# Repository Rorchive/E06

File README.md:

<div align="center">
  
</div>

<h1 align="center">E06 Project - Analog Temperature Monitor</h1>

<p align="center">

</p>

<br>

## Overview

This project involves the development of an Analog Temperature Threshold Monitor tailored for the E06 (Analog Electronics 3) course at Inatel. The system senses temperature with an LM35 precision sensor (10 mV/°C). Its signal is conditioned by an LM324 operational amplifier in a non-inverting configuration with a gain of 10, which scales the output to 100 mV/°C. Two LM324 comparators with positive feedback (Schmitt trigger) classify the temperature into three bands: a green LED indicates T < 35 °C, a red LED indicates T > 58 °C, and both stay off in the normal range. Hysteresis of about 1 °C on each comparator eliminates output chattering caused by sensor noise near the thresholds. The green channel uses the inverting topology, and the red channel uses the non-inverting topology. Each threshold can be calibrated through Bourns 3362 trimpots, with series resistors that limit the adjustment range to ±10% for fine tuning. The hardware design runs on a symmetric ±15 V supply. It includes 1N4148 diodes that protect the LEDs against reverse voltage, an RC damper on the sensor output and local decoupling capacitors.

## Repository Organization

* `docs`: Project documentation.
* `hardware`: Native KiCad project and manufacturing files.
* `mechanics`: 3D models, technical drawings, and physical integration constraints.

## Releases

<table>
  <thead>
    <tr>
      <th>Render</th>
      <th>Hardware Revision</th>
      <th>Status</th>
      <th>Latest Release</th>
      <th>Date</th>
      <th>Datasheet</th>
      <th>BOM</th>
      <th>Manufacturing Info</th>
    </tr>
  </thead>
  <tbody>
    <tr>
      <td></td>
      <td>v1</td>
      <td>🚧 Development</td>
      <td><a href="#">-</a></td>
      <td>11-11-2026</td>
      <td><a href="#">-</a></td>
      <td><a href="#">-</a></td>
      <td><a href="#">-</a></td>
    </tr>
  </tbody>
</table>

## Fabrication

This board is intended to be fabricated using a chemical etching process. Both F.Cu and B.Cu layers are available in the [fabrication](hardware/fabrication/) folder.

## Contributing

We welcome contributions to this project! To ensure a smooth collaboration and maintain our engineering standards, please review our [Contribution Guidelines](CONTRIBUTING.md) before opening any issues, modifying the hardware design, or submitting pull requests.

## References

## License

The hardware designs and schematics are licensed under the permissive **[CERN-OHL-P-2.0](hardware/LICENSE)** open-hardware license. You are entirely free to use, modify, distribute, and commercialize the design without any copyleft obligations to share your derived works under the same terms.

---

<br/>

<div align="center">
  
</div>

<div align="center">
<sub>📜 This project is part of <strong><a href="https://github.com/Rorchive">Rorchive</a></strong>, my personal archive of activities and courses developed during my undergraduate studies at <strong>Inatel</strong>.</sub>

  <sub>Built with ❤️ by <a href="https://github.com/RodrigoCAndrade">Rodrigo Andrade</a></sub>
</div>

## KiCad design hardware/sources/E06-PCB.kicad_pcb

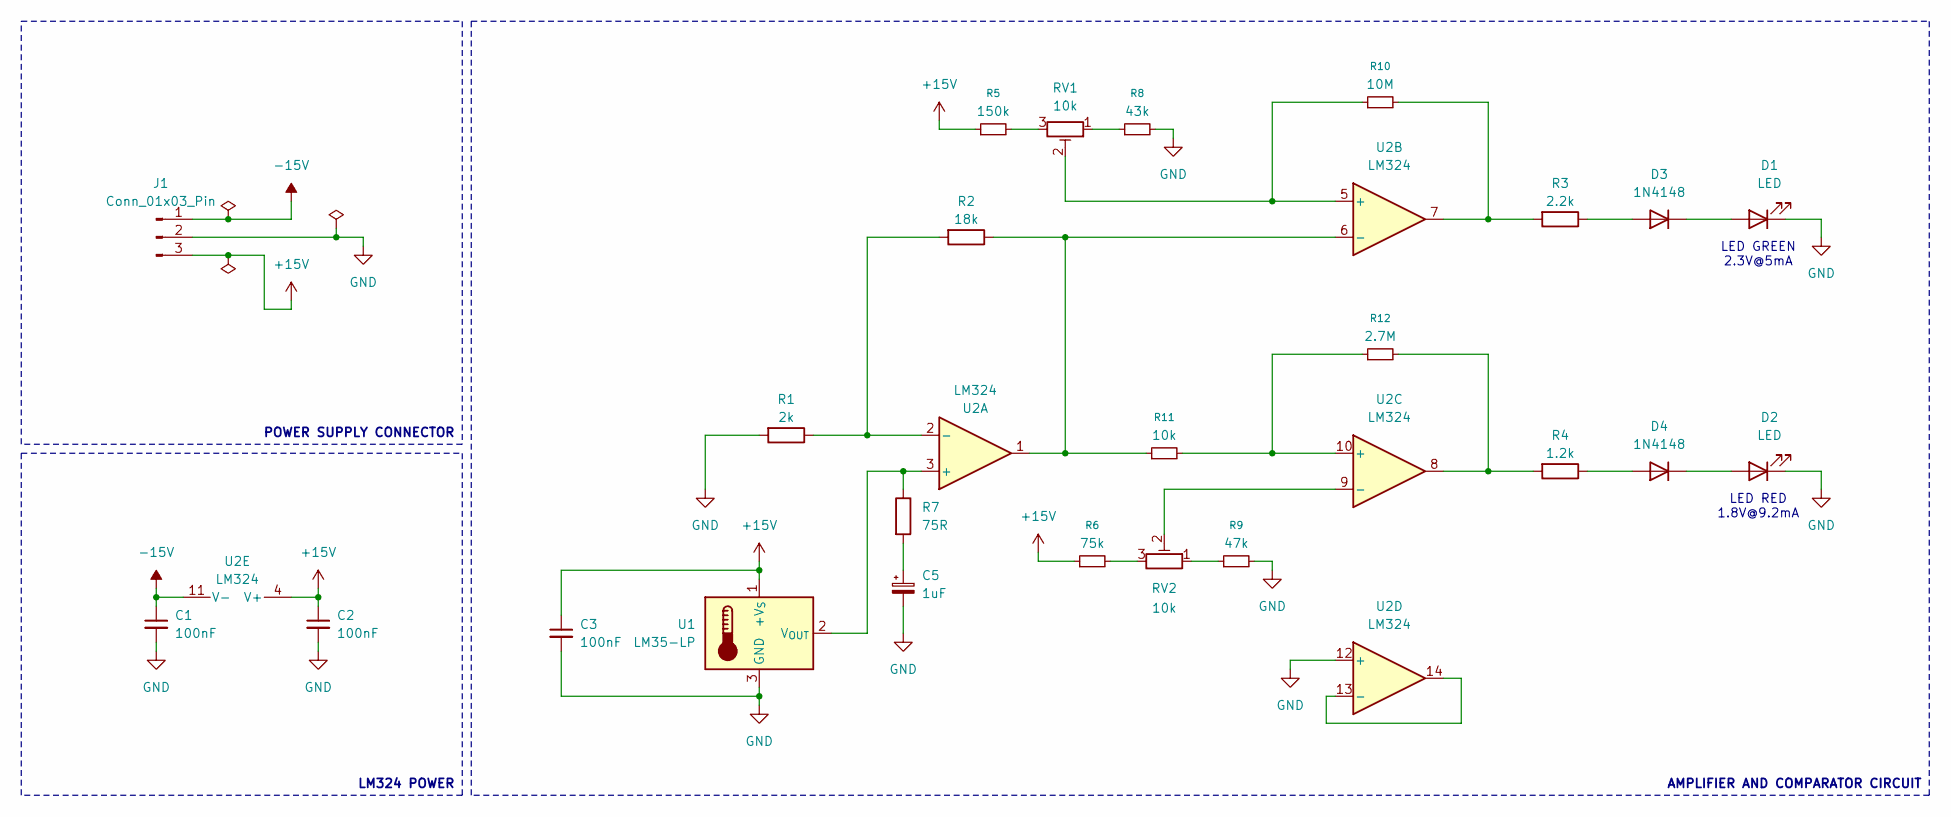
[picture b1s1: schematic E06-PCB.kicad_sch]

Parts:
C1, C2, C3: 100nF; C_Disc_D5.0mm_W2.5mm_P5.00mm
C5: 1uF; CP_Radial_D5.0mm_P2.00mm
D1, D2: LED; LED_D5.0mm
D3, D4: 1N4148; D_DO-35_SOD27_P7.62mm_Horizontal
J1: Conn_01x03_Pin; TerminalBlock_Phoenix_MKDS-1,5-3-5.08_1x03_P5.08mm_Horizont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
R1: 2k; R_Axial_DIN0207_L6.3mm_D2.5mm_P10.16mm_Horizontal
R2: 18k; R_Axial_DIN0207_L6.3mm_D2.5mm_P10.16mm_Horizontal
R3: 2.2k; R_Axial_DIN0207_L6.3mm_D2.5mm_P10.16mm_Horizontal
R4: 1.2k; R_Axial_DIN0207_L6.3mm_D2.5mm_P10.16mm_Horizontal
R5: 150k; R_Axial_DIN0207_L6.3mm_D2.5mm_P10.16mm_Horizontal
R6: 75k; R_Axial_DIN0207_L6.3mm_D2.5mm_P10.16mm_Horizontal
R7: 75R; R_Axial_DIN0207_L6.3mm_D2.5mm_P10.16mm_Horizontal
R8: 43k; R_Axial_DIN0207_L6.3mm_D2.5mm_P10.16mm_Horizontal
R9: 47k; R_Axial_DIN0207_L6.3mm_D2.5mm_P10.16mm_Horizontal
R10: 10M; R_Axial_DIN0207_L6.3mm_D2.5mm_P10.16mm_Horizontal
R11: 10k; R_Axial_DIN0207_L6.3mm_D2.5mm_P10.16mm_Horizontal
R12: 2.7M; R_Axial_DIN0207_L6.3mm_D2.5mm_P10.16mm_Horizontal
RV1, RV2: 10k; TRIM_3362P-1-103LF
U1: LM35-LP; TO-92_Wide
U2: LM324; SOIC-14_3.9x8.7mm_P1.27mm

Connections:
+15V: C2.1, C3.1, J1.3, R5.1, R6.1, U1.1 (+V_{S}), U2.4 (V+)
-15V: C1.1, J1.1, U2.11 (V-)
GND: C1.2, C2.2, C3.2, C5.2, D1.1 (K), D2.1 (K), J1.2, R1.2, R8.2, R9.2, U1.3 (GND), U2.12 (+)
unnamed: C5.1, R7.2
unnamed: D1.2 (A), D3.1 (K)
unnamed: D2.2 (A), D4.1 (K)
unnamed: D3.2 (A), R3.1
unnamed: D4.2 (A), R4.1
unnamed: R5.2, RV1.3
unnamed: R6.2, RV2.3
unnamed: R8.1, RV1.1
unnamed: R9.1, RV2.1
unnamed: R3.2, R10.2, U2.7
unnamed: R4.2, R12.2, U2.8
unnamed: R7.1, U1.2 (V_{OUT}), U2.3 (+)
unnamed: R1.1, R2.2, U2.2 (-)
unnamed: R10.1, RV1.2, U2.5 (+)
unnamed: R2.1, R11.1, U2.1, U2.6 (-)
unnamed: R11.2, R12.1, U2.10 (+)
unnamed: RV2.2, U2.9 (-)
unnamed: U2.13 (-), U2.14

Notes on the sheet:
LED RED 1.8V@9.2mA
LED GREEN 2.3V@5mA
AMPLIFIER AND COMPARATOR CIRCUIT
LM324 POWER
POWER SUPPLY CONNECTOR

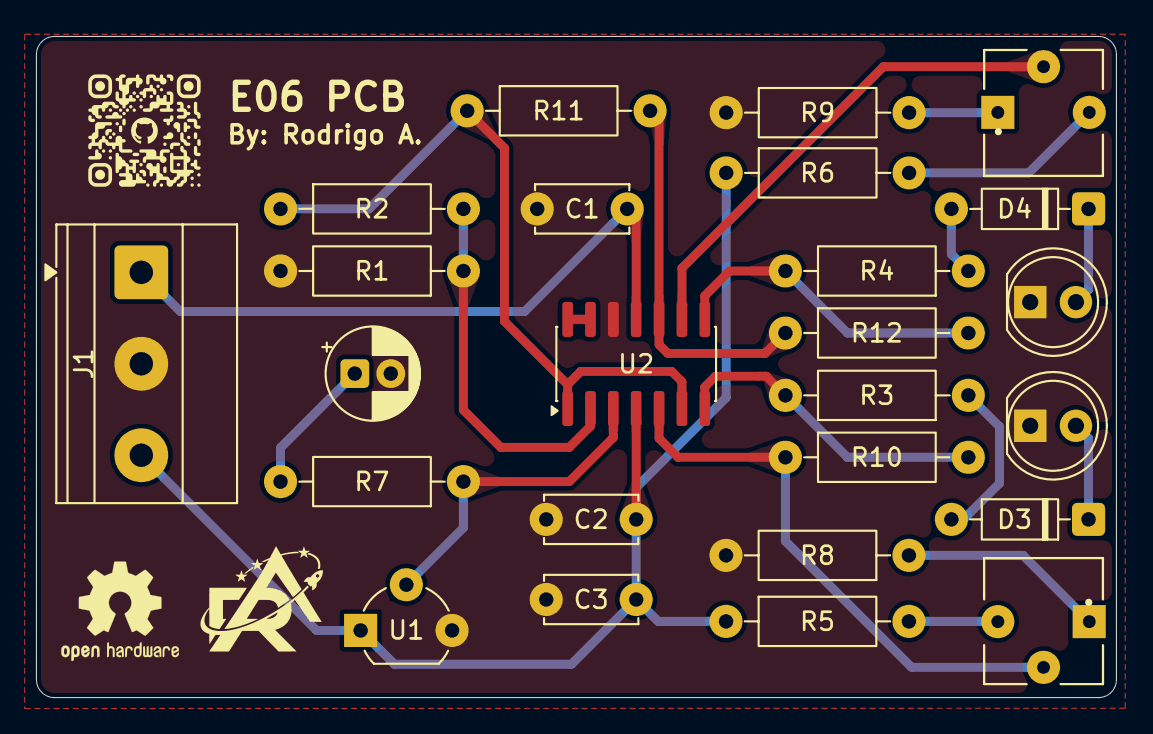
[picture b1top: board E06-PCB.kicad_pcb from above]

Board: 2 copper layers, 60.0 x 36.7 mm, 25 parts (0 on the bottom side), 21 nets.
